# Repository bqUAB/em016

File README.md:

em016
=====

Augmented Reality with DLPs

Source code and related files for the design of [Augmented Reality with DLPs](http://www.innovatefpga.com/cgi-bin/innovate/teams.pl?Id=EM016)

The project proposal was submitted to the [Innovate FPGA](http://www.innovatefpga.com/em/index.html) contest.

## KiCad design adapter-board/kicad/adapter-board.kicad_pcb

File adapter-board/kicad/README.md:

Adapter Board
=============

This directory contains the KiCad project and its corresponding files. The
board schematic is finished but the PCB is not. To commit the correct files the
guide found at [Massaging your git for kicad](https://jnavila.github.io/plotkicadsch/)
was followed.

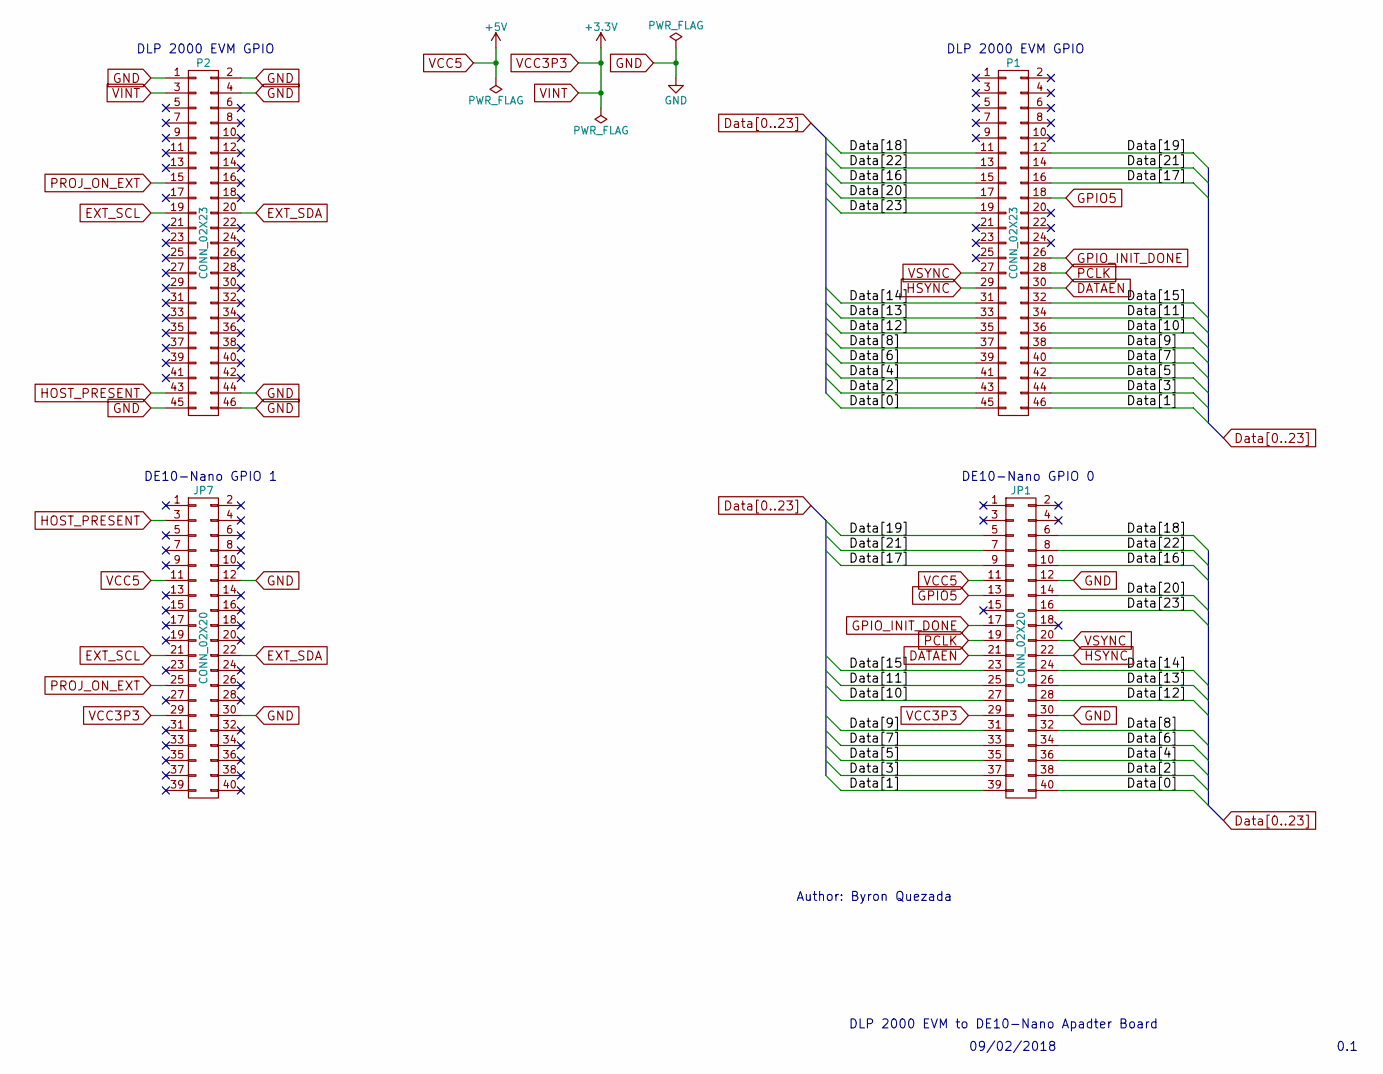
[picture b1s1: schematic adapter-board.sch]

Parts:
JP1, JP7: CONN_02X20; Socket_Strip_Straight_2x20_Pitch2.54mm
P1, P2: CONN_02X23; Socket_Strip_Straight_2x23_Pitch2.54mm

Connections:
/Data[0]: JP1.40, P1.45
/Data[1]: JP1.39, P1.46
/Data[2]: JP1.38, P1.43
/Data[3]: JP1.37, P1.44
/Data[4]: JP1.36, P1.41
/Data[5]: JP1.35, P1.42
/Data[6]: JP1.34, P1.39
/Data[7]: JP1.33, P1.40
/Data[8]: JP1.32, P1.37
/Data[9]: JP1.31, P1.38
/Data[10]: JP1.27, P1.36
/Data[11]: JP1.25, P1.34
/Data[12]: JP1.28, P1.35
/Data[13]: JP1.26, P1.33
/Data[14]: JP1.24, P1.31
/Data[15]: JP1.23, P1.32
/Data[16]: JP1.10, P1.15
/Data[17]: JP1.9, P1.16
/Data[18]: JP1.6, P1.11
/Data[19]: JP1.5, P1.12
/Data[20]: JP1.14, P1.17
/Data[21]: JP1.7, P1.14
/Data[22]: JP1.8, P1.13
/Data[23]: JP1.16, P1.19
DATAEN: JP1.21, P1.30
EXT_SCL: JP7.21, P2.19
EXT_SDA: JP7.22, P2.20
GND: JP1.12, JP1.30, JP7.12, JP7.30, P2.1, P2.2, P2.4, P2.44, P2.45, P2.46
GPIO5: JP1.13, P1.18
GPIO_INIT_DONE: JP1.17, P1.26
HOST_PRESENT: JP7.3, P2.43
HSYNC: JP1.22, P1.29
PCLK: JP1.19, P1.28
PROJ_ON_EXT: JP7.25, P2.15
VCC3P3: JP1.29, JP7.29, P2.3
VCC5: JP1.11, JP7.11
VSYNC: JP1.20, P1.27

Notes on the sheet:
09/02/2018
0.1
DLP 2000 EVM to DE10-Nano Apadter Board
DE10-Nano GPIO 0
DLP 2000 EVM GPIO
Author: Byron Quezada
DE10-Nano GPIO 1

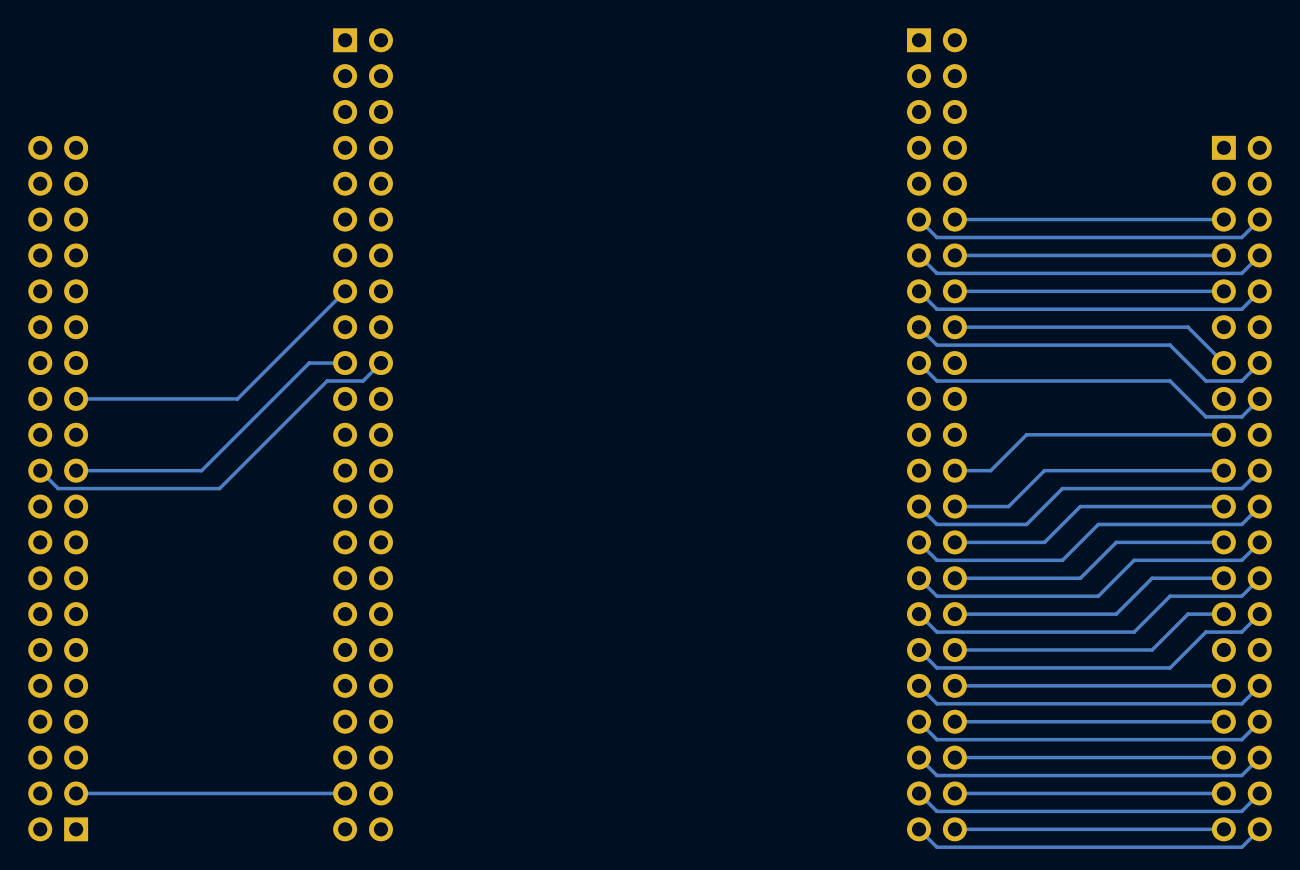
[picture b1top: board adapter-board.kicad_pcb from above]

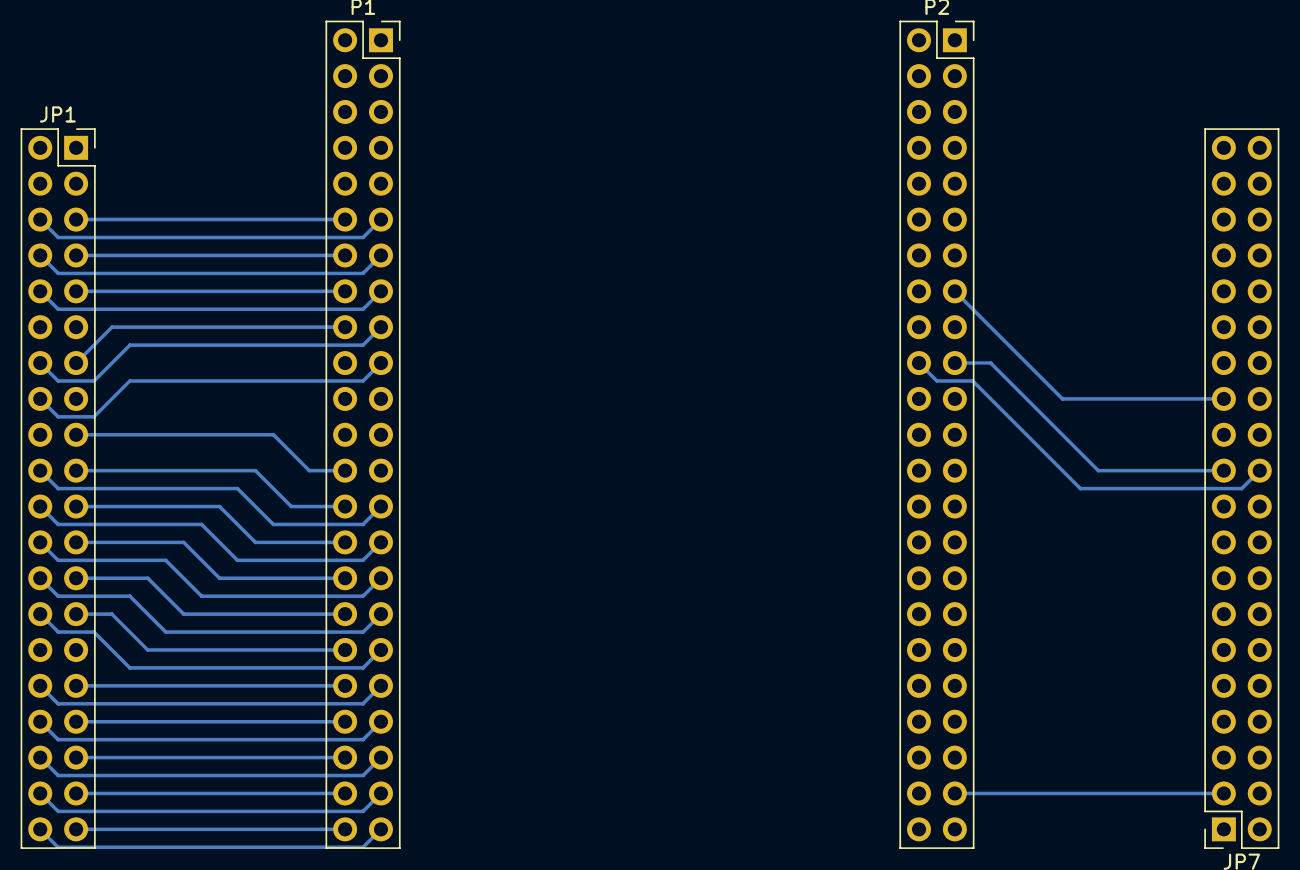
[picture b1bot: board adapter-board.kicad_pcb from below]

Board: 2 copper layers, 4 parts (4 on the bottom side), 37 nets.

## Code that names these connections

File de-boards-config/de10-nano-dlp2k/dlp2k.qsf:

# -------------------------------------------------------------------------- #
#
# Copyright (C) 2017  Intel Corporation. All rights reserved.
# Your use of Intel Corporation's design tools, logic functions 
# and other software and tools, and its AMPP partner logic 
# functions, and any output files from any of the foregoing 
# (including device programming or simulation files), and any 
# associated documentation or information are expressly subject 
# to the terms and conditions of the Intel Program License 
# Subscription Agreement, the Intel Quartus Prime License Agreement,
# the Intel MegaCore Function License Agreement, or other 
# applicable license agreement, including, without limitation, 
# that your use is for the sole purpose of programming logic 
# devices manufactured by Intel and sold by Intel or its 
# authorized distributors.  Please refer to the applicable 
# agreement for further details.
#
# -------------------------------------------------------------------------- #
#
# Quartus Prime
# Version 16.1.2 Build 203 01/18/2017 SJ Lite Edition
# Date created = 11:16:38  April 20, 2018
#
# -------------------------------------------------------------------------- #
#
# Notes:
#
# 1) The default values for assignments are stored in the file:
#		dlp2k_assignment_defaults.qdf
#    If this file doesn't exist, see file:
#		assignment_defaults.qdf
#
# 2) Altera recommends that you do not modify this file. This
#    file is updated automatically by the Quartus Prime software
#    and any changes you make may be lost or overwritten.
#
# -------------------------------------------------------------------------- #


set_global_assignment -name FAMILY "Cyclone V"
set_global_assignment -name DEVICE 5CSEBA6U23I7DK
set_global_assignment -name TOP_LEVEL_ENTITY dlp2k
set_global_assignment -name ORIGINAL_QUARTUS_VERSION 16.1.2
set_global_assignment -name PROJECT_CREATION_TIME_DATE "11:16:37  APRIL 20, 2018"
set_global_assignment -name LAST_QUARTUS_VERSION "16.1.2 Lite Edition"
set_global_assignment -name PROJECT_OUTPUT_DIRECTORY output_files
set_global_assignment -name MIN_CORE_JUNCTION_TEMP "-40"
set_global_assignment -name MAX_CORE_JUNCTION_TEMP 100
set_global_assignment -name ERROR_CHECK_FREQUENCY_DIVISOR 256
set_global_assignment -name PARTITION_NETLIST_TYPE SOURCE -section_id Top
set_global_assignment -name PARTITION_FITTER_PRESERVATION_LEVEL PLACEMENT_AND_ROUTING -section_id Top
set_global_assignment -name PARTITION_COLOR 16764057 -section_id Top
set_instance_assignment -name IO_STANDARD "3.3-V LVTTL" -to rst
set_instance_assignment -name IO_STANDARD "3.3-V LVTTL" -to clk
set_instance_assignment -name IO_STANDARD "3.3-V LVTTL" -to vsync
set_instance_assignment -name IO_STANDARD "3.3-V LVTTL" -to hsync
set_location_assignment PIN_AH17 -to rst
set_location_assignment PIN_V11 -to clk
set_location_assignment PIN_AD20 -to vsync
set_location_assignment PIN_AD17 -to hsync
set_location_assignment PIN_AA11 -to data[0]
set_location_assignment PIN_AA13 -to data[1]
set_location_assignment PIN_AA26 -to data[2]
set_location_assignment PIN_Y11 -to data[3]
set_location_assignment PIN_AB26 -to data[4]
set_location_assignment PIN_AB25 -to data[5]
set_location_assignment PIN_Y17 -to data[6]
set_location_assignment PIN_Y18 -to data[7]
set_location_assignment PIN_W14 -to data[8]
set_location_assignment PIN_AA18 -to data[9]
set_location_assignment PIN_AA19 -to data[10]
set_location_assignment PIN_Y19 -to data[11]
set_location_assignment PIN_W11 -to data[12]
set_location_assignment PIN_AB23 -to data[13]
set_location_assignment PIN_AC22 -to data[14]
set_location_assignment PIN_AC23 -to data[15]
set_location_assignment PIN_AH3 -to data[16]
set_location_assignment PIN_AF4 -to data[17]
set_location_assignment PIN_AH13 -to data[18]
set_location_assignment PIN_D8 -to data[19]
set_location_assignment PIN_AG14 -to data[20]
set_location_assignment PIN_AF7 -to data[21]
set_location_assignment PIN_AH14 -to data[22]
set_location_assignment PIN_AE6 -to data[23]
set_instance_assignment -name IO_STANDARD "3.3-V LVTTL" -to data[23]
set_instance_assignment -name IO_STANDARD "3.3-V LVTTL" -to data[22]
set_instance_assignment -name IO_STANDARD "3.3-V LVTTL" -to data[21]
set_instance_assignment -name IO_STANDARD "3.3-V LVTTL" -to data[20]
set_instance_assignment -name IO_STANDARD "3.3-V LVTTL" -to data[19]
set_instance_assignment -name IO_STANDARD "3.3-V LVTTL" -to data[18]
set_instance_assignment -name IO_STANDARD "3.3-V LVTTL" -to data[17]
set_instance_assignment -name IO_STANDARD "3.3-V LVTTL" -to data[16]
set_instance_assignment -name IO_STANDARD "3.3-V LVTTL" -to data[15]
set_instance_assignment -name IO_STANDARD "3.3-V LVTTL" -to data[14]
set_instance_assignment -name IO_STANDARD "3.3-V LVTTL" -to data[13]
set_instance_assignment -name IO_STANDARD "3.3-V LVTTL" -to data[12]
set_instance_assignment -name IO_STANDARD "3.3-V LVTTL" -to data[11]
set_instance_assignment -name IO_STANDARD "3.3-V LVTTL" -to data[10]
set_instance_assignment -name IO_STANDARD "3.3-V LVTTL" -to data[9]
set_instance_assignment -name IO_STANDARD "3.3-V LVTTL" -to data[8]
set_instance_assignment -name IO_STANDARD "3.3-V LVTTL" -to data[7]
set_instance_assignment -name IO_STANDARD "3.3-V LVTTL" -to data[6]
set_instance_assignment -name IO_STANDARD "3.3-V LVTTL" -to data[5]
set_instance_assignment -name IO_STANDARD "3.3-V LVTTL" -to data[4]
set_instance_assignment -name IO_STANDARD "3.3-V LVTTL" -to data[3]
set_instance_assignment -name IO_STANDARD "3.3-V LVTTL" -to data[2]
set_instance_assignment -name IO_STANDARD "3.3-V LVTTL" -to data[1]
set_instance_assignment -name IO_STANDARD "3.3-V LVTTL" -to data[0]
set_location_assignment PIN_W15 -to led[0]
set_location_assignment PIN_AA24 -to led[1]
set_location_assignment PIN_V16 -to led[2]
set_instance_assignment -name IO_STANDARD "3.3-V LVTTL" -to led[2]
set_instance_assignment -name IO_STANDARD "3.3-V LVTTL" -to led[1]
set_instance_assignment -name IO_STANDARD "3.3-V LVTTL" -to led[0]
set_global_assignment -name POWER_PRESET_COOLING_SOLUTION "23 MM HEAT SINK WITH 200 LFPM AIRFLOW"
set_global_assignment -name POWER_BOARD_THERMAL_MODEL "NONE (CONSERVATIVE)"
set_global_assignment -name VHDL_FILE ../../../../Documents/GitHub/em016/vhdl/shift_reg.vhd
set_global_assignment -name VHDL_FILE ../../../../Documents/GitHub/em016/vhdl/bin_counter.vhd
set_global_assignment -name VHDL_FILE ../../../../Documents/GitHub/em016/vhdl/vga_sync.vhd
set_global_assignment -name VHDL_FILE ../../../../Documents/GitHub/em016/vhdl/ram.vhd
set_global_assignment -name VHDL_FILE ../../../../Documents/GitHub/em016/vhdl/pos_xy.vhd
set_global_assignment -name VHDL_FILE ../../../../Documents/GitHub/em016/vhdl/dlp2k.vhd
set_global_assignment -name VHDL_FILE ../../../../Documents/GitHub/em016/vhdl/decoder.vhd
set_location_assignment PIN_AF26 -to led[4]
set_location_assignment PIN_V15 -to led[3]
set_instance_assignment -name IO_STANDARD "3.3-V LVTTL" -to led[4]
set_instance_assignment -name IO_STANDARD "3.3-V LVTTL" -to led[3]
set_instance_assignment -name IO_STANDARD "3.3-V LVTTL" -to led
set_location_assignment PIN_C12 -to dataen
set_instance_assignment -name IO_STANDARD "3.3-V LVTTL" -to dataen
set_location_assignment PIN_D12 -to pclk
set_instance_assignment -name IO_STANDARD "3.3-V LVTTL" -to pclk
set_location_assignment PIN_AD5 -to gpio5
set_location_assignment PIN_AD23 -to gpio_init_done
set_location_assignment PIN_AA15 -to host_presentz
set_location_assignment PIN_AF22 -to proj_on_ext
set_instance_assignment -name IO_STANDARD "3.3-V LVTTL" -to proj_on_ext
set_instance_assignment -name IO_STANDARD "3.3-V LVTTL" -to host_presentz
set_instance_assignment -name IO_STANDARD "3.3-V LVTTL" -to gpio_init_done
set_instance_assignment -name IO_STANDARD "3.3-V LVTTL" -to gpio5
set_instance_assignment -name PARTITION_HIERARCHY root_partition -to | -section_id Top

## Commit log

2018-02-13 Updated Readme
    Brief description of the repository contents
2018-02-13 Added DE0 VGA bypass
2018-02-13 Created Kicad directory README.md
2018-02-13 Added KiCad project and pdf
2018-02-15 DE0 GPIO0 to VGA 0v2
    Changed the pinout and improved the csv file with more information about
    (fixes #2 )
2018-02-15 Uploaded Altium project.
    Completes #5
2018-02-15 Improved directory structure
    Grouped the DE boards projects, configurations, etc. into one directory.
2018-02-15 Added DE0-Nano-SoC VGA test
2018-02-15 Added VGA sync testbench
    Tested to be working. Closes #16
2018-02-20 Added RAM VHDL and testbench
    Closes #24
2018-02-20 Added README
2018-02-20 Started_i2c_clk_generator
    Making the harwdare that outputs 100Khz frecuency from 50 Mhz input frecuency
2018-02-20 Change
    Test a change to see the effects
2018-02-23 Added dot tracking and px generator circuits
    Have to adapt them to our current application.
2018-02-23 README modifications.
    Created the DE10-Nano to DLP 2000 EVM pinout map.
    Improved the DE0-Nano-SoC VGA test README.
    Renamed the faulty DE-boards README.
2018-02-23 Added csv pinout and improved READMEs
2018-02-23 Added and improved READMEs
2018-02-26 i2c_clk
    I2C_clk file is used to fuse the two components (toggle flip flop and a divider). The objective was to make from 50Mhz frecuency a 100KHz frecuency required for I2C bus clock
2018-03-01 quartus_i2c_qar
    This file contains a packet with simulations of the 100Khz SCL signal requier for I2C clock. Files are tested and proper functionality is guaranteed
2018-03-01 Update
    This is the last change of code update. Finished clk generator module
2018-03-02 Added tested code and gitignore
2018-03-02 Compatibility tested
2018-03-09 Rearrange
    Tb files in a folder apart. Merged code in de-0
2018-03-12 No longer using switches as input
2018-03-12 Added PATH configuration script
2018-03-19 Added gitignore
2018-03-19 Added I2C bus class
2018-03-19 Minor library calls update
    Change done to adjust for separate source and include folders
2018-04-06 Added DE10-Nano VGA test
2018-04-10 Added frame buffer draft
2018-04-16 Added dlp source file
2018-04-16 Added dlp initialization
2018-04-16 Updated I2C library
2018-04-16 Added dlpc2607 source files for dlp configuration
2018-04-16 Added GPIO to DLP EVM test
    Working with all outputs driving ground. One of the four signals turns off the DLP EVM.
2018-04-17 Added partially working VGA test
    Red value works fine, Blue value seems working but it's not comparable as the white value appears light blue.
2018-04-17 Deleted whitespace
2018-04-18 Added FPGA to DLP demo
2018-04-23 Added framebuffer vhdl draft
2018-04-23 Added UAB drafts
2018-06-07 Added binary counter and testbench
2018-06-07 Changed data input to binary counter
    Result too fast to analyze proper behaviour.
2018-06-07 Color sweep demo
2018-06-08 Added shift register with testbench
2018-06-12 Shifter + counter
    Non successful
2018-06-12 Added decoded sweep demo
2018-06-13 Improved and slower sweep demo
2018-06-14 Added full sweep demo
